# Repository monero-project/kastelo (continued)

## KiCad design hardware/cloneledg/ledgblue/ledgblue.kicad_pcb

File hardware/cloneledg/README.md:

# Hardware Cloneledg Design

One paragraph of descriptive text.

## Getting Started

Example text to help understand contents and subdirectories.

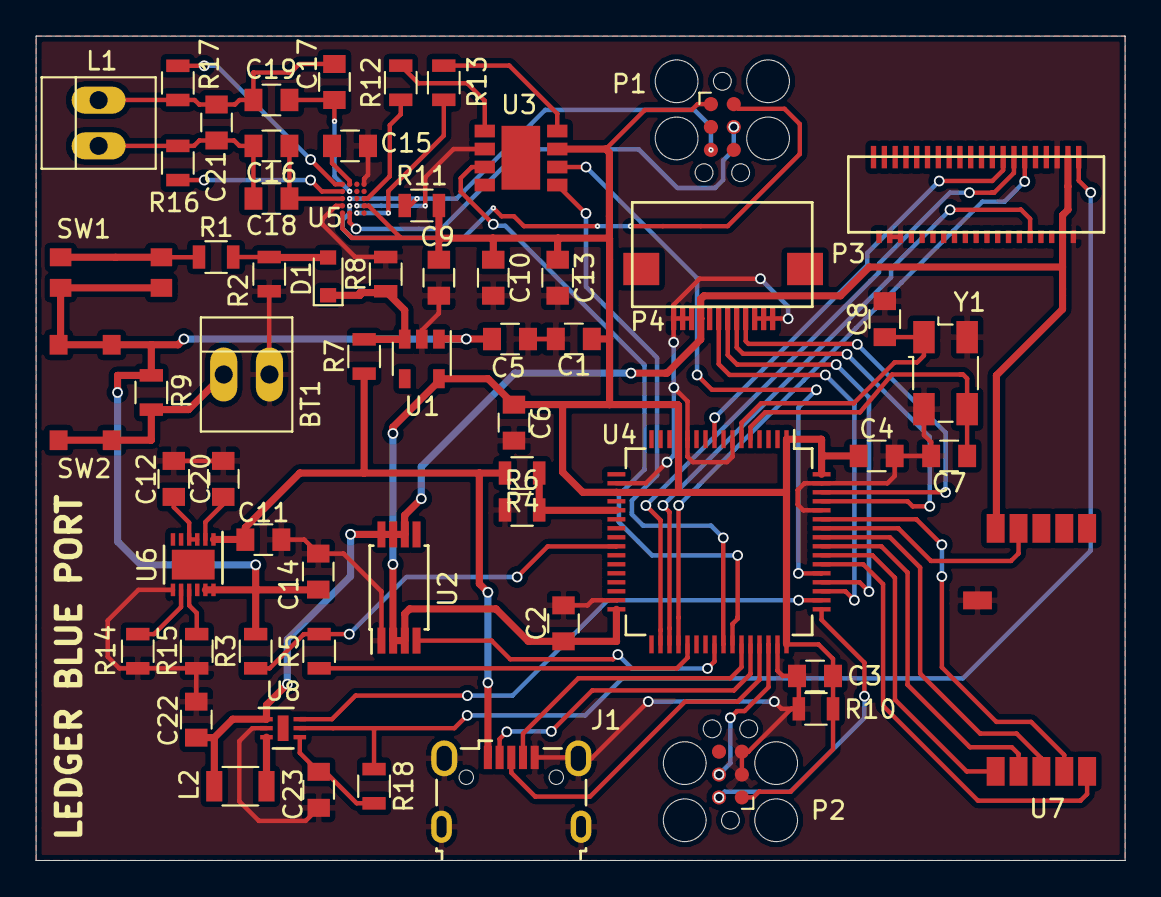
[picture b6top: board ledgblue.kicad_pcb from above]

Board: 2 copper layers, 60.5 x 45.8 mm, 61 parts (0 on the bottom side), 59 nets.

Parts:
BT1: Battery; PINHEAD1-2
C1, C2, C3, C4, C9, C13: 100nF; C_0805
C5, C6, C22, C23: 1uF; C_0805
C7, C8: 20pF; C_0805
C10, C14: 4.7uF; C_0805
C11, C12, C20: 2.2uF; C_0805
C15: 15nF; C_0805
C16, C17: 27pF; C_0805
C18, C19: 180pF; C_0805
C21: 39pF; C_0805
D1: D_Schottky; D_0805
J1: USB_OTG; USB_Micro-B_Wuerth-629105150521
L1: Antenna; PINHEAD1-2
L2: 10uH; L_1206
P1, P2: DEBUG; Tag-Connect_TC2030-IDC-FP
P3: YL035MY2; hiroseFH23-39S
P4: YL035MY2_TS_WURTH; wurth687-112-149-022
R1, R2, R14: 10k; R_0805
R3, R4, R5, R6: 1.2k; R_0805
R7: 680k; R_0805
R8: 1M; R_0805
R9, R12, R13, R16, R17: 0; R_0805
R10, R11: 100k; R_0805
R15: 1k; R_0805
R18: 10; R_0805
SW1: WURTH 436353045816; wurth436353045816
SW2: SW-PB; multicompMCFTE-3C-V
U1: LD39020_3.0V; SOT-23-5
U2: STMPS2151TTR; TSSOP-8_4.4x3mm_Pitch0.65mm
U3: ST31G480
U4: STM32L476RCT6; LQFP-64_10x10mm_Pitch0.5mm
U5: AMS_AS3921; amsAS3921
U6: STNS01PUR; DFN-12-1EP_3x3mm_Pitch0.45mm
U7: SPBTLE-RF; STSPBTLE-RF
U8: STLA02PUR; DFN-6-1EP_2x2mm_Pitch0.5mm
Y1: 8 MHz; Crystal_SMD_Abracon_ABM3B-4pin_5.0x3.2mm

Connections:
+BATT: C5.1, C14.2, R3.2, R9.1, SW1.1, SW2.1, U1.1, U6.11, U6.12
AUX_PWR: C22.2, L2.2, P3.3, P3.4, P4.9, U2.6, U2.7, U2.8, U7.5, U8.1
AUX_PWR_enable: U2.4, U4.40
BC_ADC_EN: R5.1, U4.37
BC_ADC_IN: R3.1, R5.2, U4.25
BLE_CS: U4.59, U7.10
BLE_IRQ: U4.58, U7.4
BLE_MISO: U4.56, U7.8
BLE_MOSI: U4.57, U7.9
BLE_RST: U4.54, U7.11
BLE_SCK: U4.55, U7.7
Backlight_PWM: U4.50, U8.6
ButtonIT: D1.2, R1.2, R2.1
DISP_SCL: P3.13, U4.34
Disp_CS: P3.10, U4.35
Disp_RESET: P3.15, U4.9
Disp_SDA: P3.11, U4.36
LED_A: P3.1, R18.1, U8.5
MAIN_POWER: C1.1, C2.1, C3.1, C4.1, C6.1, C9.1, C10.1, C13.1, P1.1, P2.1, R10.2, R11.2, U1.5, U2.2, U2.3, U3.7, U4.1, U4.13, U4.19, U4.32, U4.48, U4.64, U5.A4, U5.D5
NRST: BT1.2, C1.2, C2.2, C3.2, C4.2, C5.2, C6.2, C7.2, C8.2, C9.2, C10.2, C11.2, C12.2, C13.2, C14.1, C15.2, C20.1, C22.1, C23.2, J1.5, J1.6, P2.3, P2.5, P3.2, P3.5, P3.34, P3.36, P4.1, P4.2, P4.3, P4.10, P4.11, P4.12, R2.2, R6.1, R8.2, R10.1, R14.2, R15.2, U1.2, U2.1, U3.2, U4.7, U4.12, U4.18, U4.31, U4.47, U4.60, U4.63, U5.A1, U5.B1, U5.B4, U5.D4, U6.7, U7.6, U8.2, Y1.2, Y1.4
unnamed: BT1.1, R9.2, SW2.2
unnamed: C7.1, U4.5, Y1.3
unnamed: C8.1, U4.6, Y1.1
unnamed: C12.1, U6.2
unnamed: C15.1, U5.C1
unnamed: C16.1, C18.1, U5.D3
unnamed: C16.2, C18.2, C21.1, L1.1, R16.1
unnamed: C17.1, C19.1, U5.C2
unnamed: C17.2, C19.2, C21.2, L1.2, R17.1
unnamed: C20.2, U6.3, U6.4
unnamed: C23.1, R18.2, U8.4
unnamed: D1.1, R7.2, R8.1, U1.3
unnamed: L2.1, U8.3
unnamed: P1.2, U5.C4
unnamed: P1.4, U5.C5
unnamed: P1.5, R11.1, U5.C3
unnamed: R1.1, SW1.2
unnamed: R12.1, U5.A3
unnamed: R12.2, U3.1
unnamed: R13.1, U5.B5
unnamed: R13.2, U3.8
unnamed: R14.1, U6.8
unnamed: R15.1, U6.9
unnamed: R16.2, U5.D2
unnamed: R17.2, U5.D1
SE_CLK: U3.5, U4.41
SE_IO: U3.3, U4.42
SE_RST: U3.6, U4.53
SWCLK: P2.2, U4.49
SWIO: P2.4, U4.46
TS_CE: P4.7, U4.51
TS_IRQ: P4.6, U4.52
TS_SCL: P4.5, U4.61
TS_SDA: P4.4, U4.62
USBDM: J1.2, U4.44
USBDP: J1.3, U4.45
USBID: J1.4, U4.43
VBUS: C11.1, J1.1, R4.2, R7.1, U6.1
VBUS_PRE: R4.1, R6.2, U4.21

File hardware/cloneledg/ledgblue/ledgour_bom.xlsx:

| Ledgour BoM | Updated: 2018-01-07
 | Name | Package | Designation | Qty | Link | Alternative link
 | C1,C2,C3,C4,C9,C13 | C_0805 | 0.1uF | 6 | https://www.arrow.com/en/products/vj0805y104jxxcw1bc/vishay
 | C5,C6,C22,C23 | C_0805 | 1uF | 4 | https://www.arrow.com/en/products/vj0805y105jxqtw1bc/vishay
 | C7,C8 | C_0805 | 20pF | 2 | https://www.arrow.com/en/products/nmc0805npo200j50trpf/nic-c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
 | C10,C14 | C_0805 | 4.7uF | 2 | https://www.arrow.com/en/products/vj0805v475zxqtw1bc/vishay
 | C11,C12,C20 | C_0805 | 2.2uF | 3 | https://www.arrow.com/en/products/vj0805g225kxqtw1bc/vishay
 | C15 | C_0805 | 0.015uF | 1 | https://www.arrow.com/en/products/cl21b153kbannnc/samsung-el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
 | C16,C17 | C_0805 | 27pF | 2 | https://www.arrow.com/en/products/cl21c270jbannnc/samsung-el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
 | C18,C19 | C_0805 | 180pF | 2 | https://www.arrow.com/en/products/cl21c181jbannnd/samsung-el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
 | C21 | C_0805 | 39pF | 1 | https://www.arrow.com/en/products/cl21c390jbannnc/samsung-el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
 | R1,R2,R14 | R_0805 | 10k | 3 | https://www.arrow.com/en/products/crcw080510k0jnea/vishay
 | R3,R4,R5,R6 | R_0805 | 1.2k | 4 | https://www.arrow.com/en/products/crcw08051k20fkea/vishay
 | R7 | R_0805 | 680k | 1 | https://www.arrow.com/en/products/crcw0805680kfkea/vishay
 | R8 | R_0805 | 1M | 1 | https://www.arrow.com/en/products/crcw08051m00jneahp/vishay
 | R9,R12,R13,R16,R17 | R_0805 | 0 | 5 | https://www.arrow.com/en/products/rca08050000zsea/vishay
 | R10,R11 | R_0805 | 100k | 2 | https://www.arrow.com/en/products/crcw0805100kfkeb/vishay
 | R15 | R_0805 | 1k | 1 | https://www.arrow.com/en/products/crcw08051k00jnta/vishay
 | R18 | R_0805 | 10 | 1 | https://www.arrow.com/en/products/crcw080510r0jnea/vishay
 | BT1 | PINHEAD1-2 | Battery | 1 | https://www.arrow.com/en/products/0901200778/molex
 | L1 | PINHEAD1-2 | Antenna | 1 | https://www.arrow.com/en/products/0901200778/molex
 | L2 | L_1206 | 10uH | 1 | https://www.arrow.com/en/products/nlcv32t-100k-pfr/tdk
 | D1 | D_0805 | D_Schottky | 1 | https://www.arrow.com/en/products/sd0805s020s0r5/avx
 | SW1 | wurth436353045816 | WURTH 436353045816 | 1 | http://uk.farnell.com/wurth-elektronik/436353045816/switch-1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 | https://www.digikey.com/product-detail/en/wurth-electronics-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
 | SW2 | multicompMCFTE-3C-V | SW-PB | 1 | http://uk.farnell.com/multicomp/mcfte-3c-v/switch-micro-dete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
 | U1 | SOT-23-5 | LD39020 | 1 | https://www.arrow.com/en/products/ld39020adm30r/stmicroelectronics
 | U2 | TSSOP-8_4.4x3mm_Pitch0.65mm | STMPS2151TTR | 1 | https://www.arrow.com/en/products/stmps2151ttr/stmicroelectronics | https://www.mouser.de/ProductDetail/STMicroelectronics/STMPS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
 | U3 | WLCSP | ST31G480 | 1 | N/A to due NDA
 | U4 | LQFP-64_10x10mm_Pitch0.5mm | STM32L476RCT6 | 1 | https://www.arrow.com/en/products/stm32l476rct6/stmicroelectronics
 | U5 | amsAS3921 | AMS_AS3921 | 1 | https://www.arrow.com/en/products/as3921-bwlt/ams-ag | https://www.mouser.de/ProductDetail/ams/AS3921-BWLM/?qs=16w8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
 | U6 | DFN-12-1EP_3x3mm_Pitch0.45mm | STNS01PUR | 1 | https://www.arrow.com/en/products/stns01pur/stmicroelectronics
 | U7 | STSPBTLE-RF | SPBTLE-RF | 1 | https://www.arrow.com/en/products/spbtle-rf/stmicroelectronics | https://www.mouser.de/ProductDetail/STMicroelectronics/SPBTL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
 | U8 | DFN-6-1EP_2x2mm_Pitch0.5mm | STLA02PUR | 1 | https://www.arrow.com/en/products/stla02pur/stmicroelectronics | https://www.mouser.de/ProductDetail/STMicroelectronics/STLA0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
 | Y1 | 4pin_5.0x3.2mm | Abracon_ABM3B_8MHz | 1 | https://www.arrow.com/en/products/abm3b-8.000mhz-b2-t/abracon
 | P1,P2 | Tag Connect TC2030-IDC | Tag Connect TC2030-IDC | 2 | http://www.tag-connect.com/TC2030-IDC
 | P3 | hiroseFH23-39S | YL035MY2 | 1 | https://www.mouser.de/ProductDetail/?qs=0N%252bVULUZFj%2fgb7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
 | P4 | wurth687-112-149-022 | YL035MY2_TS_WURTH | 1 | https://www.mouser.de/ProductDetail/Wurth-Electronics/687112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
 | J1 | USB_Micro-B | Wuerth-629105150521 | 1 | https://www.mouser.de/productdetail/wurth-electronics/629105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

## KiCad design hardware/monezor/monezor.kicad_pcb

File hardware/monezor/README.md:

## Monezor Design Status

This was the monezor hw wallet PCB revision control.

New development of STM32 based designs throughout the project stopped after the Julian Candy released hardware revision 0.2.0.

## Exit Reasoning

STM32 integration stopped as the architecture (at least M3 based MCUs) failed to meet expectations, as well as better architectures with immutable boot and hardware cryptography appeared.

## Maintenance Plan

STM32 design is maintained in the (developer edition) Breakneck codebase, for those who prefer the architecture opposed to the advanced and improved one found in the tip master of revision control.

To find the STM32 based Breakneck codebase, switch to the _revstm_ branch:

```
$ git checkout revstm
$ cd hardware/breakneck
```

## Development Plan

New features are found in the Breakneck master codebase which migrates logic to a new consumer edition codebase as UX and functional testing mandates.

To find the current Breakneck codebase, switch to the _master_ branch:

```
$ git checkout master
$ cd hardware/breakneck
```

## New Architecture

Although nRF52840 is a candidate, the replacement for STM32 parts in new designs is CEC1702.

## Preservation Plan

The STM32 based Monezor codebase is preserved in the _revstm_ branch.

## Glossary

- **Consumer edition:** One of two Monero dedicated hardware wallet editions, integrating a well tested subset of features from the developer edition.
- **Developer edition:** One of two Monero dedicated hardware wallet editions, including all features. For example, the developer edition may contain experimental intrusion detection while the consumer edition may not (unless the features are proven stable and useful.)
- **Monezor:** The model name associated with the consumer edition.
- **Breakneck:** The model name associated with the developer edition.
- **Julian Candy:** A code name corresponding with a range of hardware revisions including 0.2.0.
- **Extra Tabulo:** A code name corresponding with a range of hardware revisions including 0.9.0.

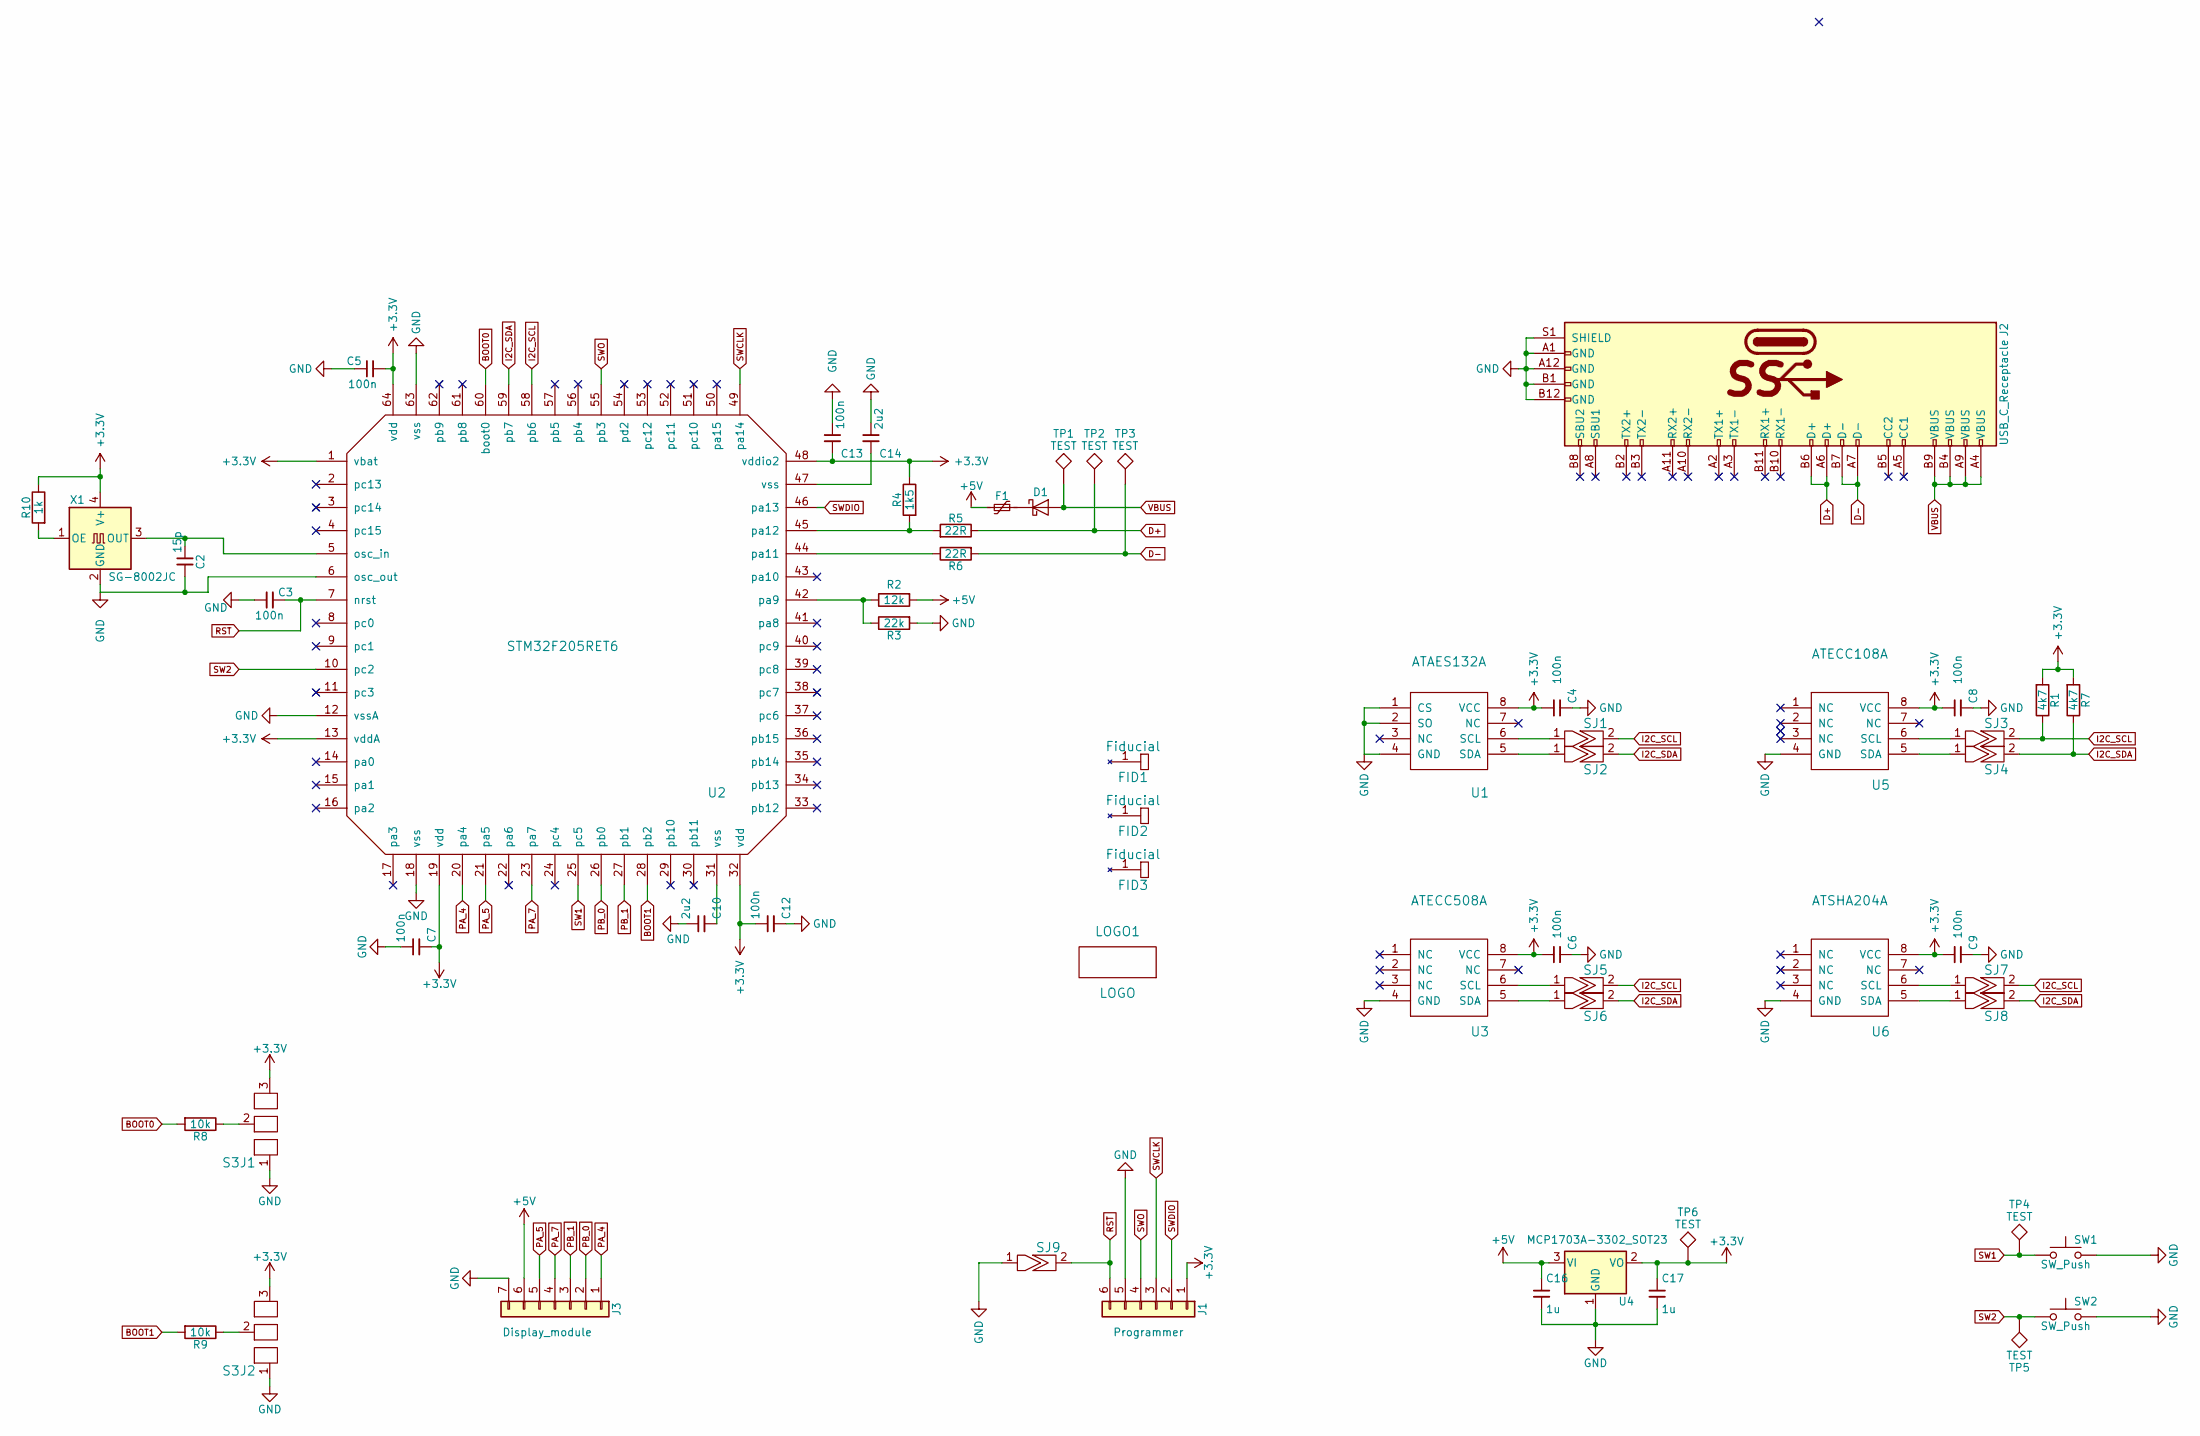
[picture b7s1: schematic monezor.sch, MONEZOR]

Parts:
C2: 15p; SMD_0805
C3, C5, C7, C12, C13: 100n; SMD_0805
C4, C6, C8, C9: 100n; SMD_0805_bottom
C10, C14: 2u2; SMD_0805
C16, C17: 1u; SMD_0805
D1: D_Schottky; D_SOD-523
F1: Polyfuse_Small; SMD_0805
FID1, FID2, FID3: Fiducial; Fiducial_Modern_SilkscreenTop
J1: Programmer; Pin_Header_Straight_1x06_Pitch2.54mm
J2: USB_C_Receptacle; USB_C_Receptacle_Amphenol_12401548E4-2A
J3: Display_module; Pin_Header_Straight_1x07_Pitch2.54mm
LOGO1: LOGO; xmr_logo
R1, R7: 4k7; SMD_0805
R2: 12k; SMD_0805
R3: 22k; SMD_0805
R4: 1k5; SMD_0805
R5, R6: 22R; SMD_0805
R8, R9: 10k; SMD_0805
R10: 1k; SMD_0805
S3J1, S3J2: solder_jumper_3pin; solder_jumper_3pin_tht_2.54
SJ1, SJ2, SJ3, SJ4, SJ5, SJ6, SJ7, SJ8: solder_jumper; solderjumper_bottom
SJ9: solder_jumper
SW1, SW2: SW_Push; BUTTON_SWITCH_SW_SPST_EVPBF
TP1, TP2, TP3, TP4, TP5, TP6: TEST; Test_Point_THT
U1: ATAES132A; SO-8_3.9x4.9mm_Pitch1.27mm_bottom
U2: STM32F205RET6; TQFP-64_10x10mm_Pitch0.5mm
U3: ATECC508A; SO-8_3.9x4.9mm_Pitch1.27mm_bottom
U4: MCP1703A-3302_SOT23; SOT-23
U5: ATECC108A; SO-8_3.9x4.9mm_Pitch1.27mm_bottom
U6: ATSHA204A; SO-8_3.9x4.9mm_Pitch1.27mm_bottom
X1: SG-8002JC; Oscillator_SMD_IQD_IQXO70-4pin_7.5x5.0mm

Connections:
+3V3: C4.2, C5.2, C6.2, C7.1, C8.2, C9.2, C12.2, C13.1, C17.1, J1.1, R1.2, R4.1, R7.2, R10.1, S3J1.3, S3J2.3, TP6.1, U1.8 (VCC), U2.1 (vbat), U2.13 (vddA), U2.19 (vdd), U2.32 (vdd), U2.48 (vddio2), U2.64 (vdd), U3.8 (VCC), U4.2 (VO), U5.8 (VCC), U6.8 (VCC), X1.4 (V+)
+5V: C16.1, F1.2, J3.6, R2.2, U4.3 (VI)
BOOT0: R8.2, U2.60 (boot0)
BOOT1: R9.2, U2.28 (pb2)
D+: J2.A6 (D+), J2.B6 (D+), R5.1, TP2.1
D-: J2.A7 (D-), J2.B7 (D-), R6.2, TP3.1
GND: C2.1, C3.2, C4.1, C5.1, C6.1, C7.2, C8.1, C9.1, C10.2, C12.1, C13.2, C14.2, C16.2, C17.2, J1.5, J2.A1 (GND), J2.A12 (GND), J2.B1 (GND), J2.B12 (GND), J2.S1 (SHIELD), J3.7, R3.2, S3J1.1, S3J2.1, SJ9.1, SW1.2, SW2.2, U1.1 (CS), U1.2 (SO), U1.4 (GND), U2.6 (osc_out), U2.12 (vssA), U2.18 (vss), U2.63 (vss), U3.4 (GND), U4.1 (GND), U5.4 (GND), U6.4 (GND), X1.2 (GND)
I2C_SCL: R1.1, SJ1.2, SJ3.2, SJ5.2, SJ7.2, U2.58 (pb6)
I2C_SDA: R7.1, SJ2.2, SJ4.2, SJ6.2, SJ8.2, U2.59 (pb7)
unnamed: C2.2, U2.5 (osc_in), X1.3 (OUT)
unnamed: C10.1, U2.31 (vss)
unnamed: C14.1, U2.47 (vss)
unnamed: D1.1 (K), F1.1
unnamed: R2.1, R3.1, U2.42 (pa9)
unnamed: R4.2, R5.2, U2.45 (pa12)
unnamed: R6.1, U2.44 (pa11)
unnamed: R8.1, S3J1.2
unnamed: R9.1, S3J2.2
unnamed: R10.2, X1.1 (OE)
unnamed: SJ1.1, U1.6 (SCL)
unnamed: SJ2.1, U1.5 (SDA)
unnamed: SJ3.1, U5.6 (SCL)
unnamed: SJ4.1, U5.5 (SDA)
unnamed: SJ5.1, U3.6 (SCL)
unnamed: SJ6.1, U3.5 (SDA)
unnamed: SJ7.1, U6.6 (SCL)
unnamed: SJ8.1, U6.5 (SDA)
PA_4: J3.1, U2.20 (pa4)
PA_5: J3.5, U2.21 (pa5)
PA_7: J3.4, U2.23 (pa7)
PB_0: J3.2, U2.26 (pb0)
PB_1: J3.3, U2.27 (pb1)
RST: C3.1, J1.6, SJ9.2, U2.7 (nrst)
SW1: SW1.1, TP4.1, U2.25 (pc5)
SW2: SW2.1, TP5.1, U2.10 (pc2)
SWCLK: J1.3, U2.49 (pa14)
SWDIO: J1.2, U2.46 (pa13)
SWO: J1.4, U2.55 (pb3)
VBUS: D1.2 (A), J2.A4 (VBUS), J2.A9 (VBUS), J2.B4 (VBUS), J2.B9 (VBUS), TP1.1

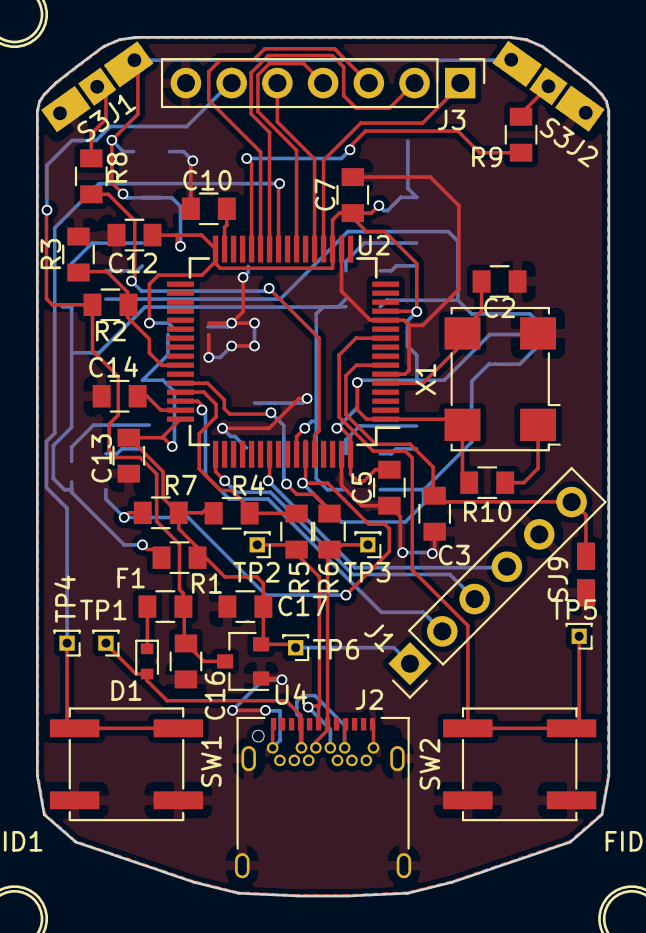
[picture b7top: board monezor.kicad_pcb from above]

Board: 2 copper layers, 31.8 x 47.7 mm, 59 parts (0 on the bottom side), 39 nets.

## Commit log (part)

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2017-10-18 Improved (enough?) location name for MCUDev derived design.
2017-10-18 Created contributing guidance document.
2017-11-10 Included location for FPGA design support and custom logic.
2017-11-11 Directed to track files in both classic and modelt versions.
2017-11-12 Hopefully practice pull request and merge workflow in team.
2017-11-12 Build in documentation of hard to remember pull request merge procedure.
2017-11-13 Correct flawed URL to avoid a HTTP 404.
2017-11-14 Added overlooked command to remove a dangling pull request branch.
2017-11-14 Created rudimentary graphics for use in print and online promotion.
2017-11-15 Created location for forthcoming antenna design in case of RF development.
2017-11-16 schematics added
2017-11-17 Created a Julian Candy manufacturing panel for single board design.
2017-11-18 Corrected minor grammar use of subject verb 'Users acknowledge.'
2017-11-19 [Task-119] Demisreablise our repository, created boilerplate (sub)titles.
2017-11-19 Edited a bit to remove accidental Kovri project residue and some 404 links.
2017-11-20 Flexible bluetooth antenna
    Flextenna BT (flexible bluetooth antenna) based on Kapton substrate, optimized for a center frequency of 2.45 GHz.
2017-11-20 Added vector exported graphics for mechanical engineering fabrication.
2017-11-20 Added installation instructions
2017-12-05 Cleaning up of file names
    Cleaned up the readme.md and filenames a bit.
2017-12-07 Cleaned up sources a bit, removing backup files and sanitised user accounts.
2017-12-09 Layout has been compacted
    The layout has been shrunk a bit. A pin header is used as placeholder for the antenna. NFC chip still not connected.
2017-12-19 Decrudified by making path names consistent and removing untracked backups.
2017-12-23 [Issue 61: Updated logo]
    A logo design suggestion for the hardware wallet project.
2017-12-31 initial blank fw
2017-12-31 submodules tweaking
2017-12-31 Corrected submodules configuration after changing subdirectory structures.
2018-01-04 Documented USB identification information pending upstream vendors.
2018-01-05 cleared warnings
2018-01-07 Reflect new USB identifiers in code pending upstream authority approval.
2018-01-07 Removed old files, after completed versions appeared named 'ledgour_bom'.
2018-01-07 usb first hello world attempts
2018-02-08 Modified to additionally avoid tracking of files in subdirectories.
2018-02-08 Corrected name of repository to recently chosen new name.
2018-02-08 Improved readme information by correcting graphic link and enlarging photos.
2018-02-10 Included display connector and Monero logo footprints in local database.
2018-02-10 Drew edge cuts, display concept, boilerplate, and dimensions.
2018-02-10 Implicitly associated default footprint for Monero logo library symbol.
2018-02-15 Corrected flawed OLED_D(0|1) anchor labels to logical display connections.
2018-02-17 Replaced a DNP zero ohm resistor with a more appropriate solder jumper.
2018-02-24 OLED: define SPISend
    - adds definition for SPISend
2018-02-26 Reluctantly added raster graphic sources for silkscreen solder mask legends.
2018-02-28 Added local copies of 3D shapes, made footprint location consistent to native KiCad, and changed holes.
2018-03-03 Corrected scaling and rotation of shapes, and connected ground paths.
2018-03-04 Moved C3 from under SW1, removed redundant SW traces, and aligned vias.
2018-03-04 Resolved unconnected bootloader and reset pins, and improved 3V3 and GND.
2018-03-05 Added pdf schematics of current design
2018-03-07 Reduced no connects further, implementing connections to +3V3 leads.
2018-03-07 Eliminated all ground lead no connect errors from the design rule check.
2018-03-08 Corrected SOT-23 3D shape absolute path, removing step and adding wings.
2018-03-08 Regenerated PDF copy of vector schematic master file.
2018-03-10 Corrected nonportable library, module, and model descriptors.
2018-03-11 Improved reset circuit by replacing with low profile angled hardware.
2018-03-15 Add disclaimer for testnet funds
2018-03-17 Added supporting structures (library, footprint, and doc) for light sensor.
2018-03-18 Integrated missing battery clip and provisional tap detector circuit.
2018-03-18 Added supporting structures (library, footprint, and model) for touch sensor.
2018-03-19 Worked around hard copy transparent background worksheet defects.
2018-03-20 Replaced hand solder DS1 with FPC connector, supporting archives only.
2018-03-25 Corrected contact numbering according to ER-OLED013A1-1W datasheet.
2018-03-27 Completed and corrected models, removed easteregg, and included datasheets.
    A number of funky hacks allow for 3D model rendering to look good, by
    specifying similar shaped packages for lacking models such as LGA-2mm
    and 6-pin LED chips. I hacked the rendering even more to represent a
    battery clip that's not the one in use at all, which could be misleading.
2018-04-01 Included recent enclosure concept sketch for Monezor consumer edition.
2018-07-15 Completed integrating and formatting ajs new text for 4-up printing.
2018-07-29 Included attribution question and answer to FAQ and bumped version.
2018-09-11 Initialised and completed first prototype design of a USB-C tester.
2018-10-09 Do a live on site conference badge super commital #HCPP18, integrating hardware design sources for the conference badge.
2018-10-25 Included prime platine changes and bump version for imminent tagging.
2018-10-25 Dumped CEC mix remastering of post STM (MCU) maintenance branching.
2018-10-26 Removed unused voltage regulator with plans to leverage CP2102N LDO.
2018-10-26 Annotated missing fiducial symbol fields in number ordered fashion.
2018-10-26 Added for USB logic a ESD protection part and supporting circuits.
2018-10-26 According to some sources, a undocumented feature is test point on NC 10.
2018-10-27 Annotated with temporary markings for PnP rails and speculative VDD.
2018-10-28 Prepared for integration of SPI quad flash storage EEPROM.
2018-10-28 Prepared for VBAT backed up state by adding CR1220 support structures.
2018-10-28 Included Dediprog (or Aardvark) compatible host adapter SPI connector.
2018-10-29 Corrected mistaken duplicate crystal resonator input entries.
2018-10-30 Documented dimensions of a typical 500 mAh 3V7 LiPo battery.
2018-10-30 Improved display connection and orientation while freeing ADC port.
2018-10-30 Removed unused (after last crystal commit) symbols and footprints.
2018-10-30 Implemented tactile switch and preliminary detector switch circuits.
2018-11-03 Implemented security enhancement as per in 4,2 ECC508 Interface Pins, specified in document CEC1702 ROM Description Addendum, Table 4-2 CEC1702 ECC508 Interface Pins.
2018-11-03 Completed CW victim south connections according to CW308_UFO_Target.
2018-11-04 Removed unused 0.7mm display pads and prepared for 24-pin additions.
2018-11-06 Annotated recently added test points pending renewed ERC testing.
2018-11-06 Added missing WFBGA footprint and shape models for CEC1702 layout.
2018-11-07 Corrected a last time towards staging display connectors before moving.
2018-11-08 Corrected missing, flawed, and other footprint package changes.
2018-11-08 Renumbered annotations to clean netlist pending start of layout.
2018-11-09 Corrected flawed symbol named with slash characters to remove them.
2018-11-09 Updated according to schematic footprint changes and added descriptions.
2018-11-10 Changed JTAG footprint, improved SAO legend, and corrected models.
2018-11-10 Made a controlled dump of recent layout changes pending arrangement.
2018-11-12 Modified trace widths and vias for consistency with design rules.
2018-11-17 Completed breakout (only betweeen edge connectors) of JTAG circuits.
2018-12-04 Regenerated netlist to accommodate recent schematic additions.
2018-12-05 Created a six up Stencil8 compliant panel using mousebite tabs.
2018-12-08 Completed conversion of manufacturing positions to special requirement.
2018-12-10 Added early state of information relating to host software plans.
2018-12-17 Integrated hex nut mounts, board guides, and adjusted length.
2018-12-24 Added enclosure top to complement bottom shell open arrangement.
2018-12-29 Released a prototype grade 35C3 badge design live on site.
2018-12-31 Documented unconnected parts to reduce unintentional short circuits.
2018-12-31 Flushed current changes to accommodate results of recent assembly tests; Introduced plastics engineering resources, made fiducial marks SMT for placing, merged SMT attribute to panel design according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
2018-12-31 Cherrypick merged 97c0734: Corrected broken link to raster circuit...
2019-01-01 Completed preparation of solderjumper integration for USBC debugging.
2019-01-03 Manually processed and recommitted placement position files.
2019-01-03 Updated page document reflecting recent graphic rendering additions.
2019-01-07 Optimised colour palette and storage using an animation filter.
2019-01-07 Increased clearanance, added license text, and made improvements.
2019-01-07 Included explicit attribution to contributors, long overdue sorry.
2019-01-07 Upgraded symbol based formats and constructs to conform with Kicad 5.0.
2019-01-07 Merged first part of bf3d6d9, debug reduction of USBC unused pins.
2019-01-07 Corrected rendered model paths and improved boot circuit silkscreen.
2019-01-07 Removed outdated prices, added potting compound, and conformal coating.
2019-01-07 Added missing minimised USB symbol structures to correct schematic.
2019-01-08 Reworked input pullups, USB-C connector, and corrected display model.
2019-01-08 Corrected solderjumpers by removing unnecessary paste layers.
2019-01-08 Added manufacturer part numbers and Octopart identifiers as needed.
2019-01-13 Merged from branch 'revstm' selective commit dc71e6a.
2019-01-13 Merged db2f2b8 from 'master' slide switch (hack) and circuitry.
2019-01-14 Corrected last remaining bottom fiducials to top and removed footprint.
2019-01-14 Included git filter configuration to control irrelevant state change.
2019-01-14 Merged 8cd1b5c from 'master' to try to control irrelevant state change.
2019-01-14 Improved file tracking ignore configuration to complete closed packages.
2019-01-17 Corrected incompatible SE (608A) timing in ROM assistance.
    This follows advice taken from Microchip case 00347747, warning against
    replacing the CEC1702 ROM addendum specification of ATECC508A with the
    more capable ATECC608A SE.
2019-01-18 Corrected only slightly flawed part make and model.
2019-01-18 Recorrected CC line pulldowns to comply with AN4775.
2019-01-18 Improve reminder message for tamper pin detector switch.
2019-01-22 Adjusted again to accommodate detector height after testing.
2019-01-23 Rerouted improved power circuit of UART bridge.
2019-02-12 Added corner pad brims to mitigate hot plate curling.
2019-02-16 Improved wording of recent STM32 integration SWD remark.
2019-03-06 Documented suspected USB controlling problem regarding HSE and LSE.
2019-03-07 Replaced SW1 to PC3(TQFP64/11) to move away from existing crystals.
2019-03-09 Added second display connector for 24-pin variants.
    This change integrates reference designs intended for 30-pin connectors
    as found in download/interfacing/ER-OLED0.96_Series_Interfacing.pdf
2019-03-28 Integrated a MCP73831 controlled lithium ion battery charger circuit.
2019-04-15 Improved annotation of untested BOOT1 pulldown circuit.
2019-04-26 Added new devkit design decoration with a lift tab adjustment?
2019-06-21 Initialised a standard PlatformIO project to host firmware sources.
2019-11-30 Dump version generated project changes pending project migration.
2019-12-02 Combined top and bottom layers for positioning import and documented.
2019-12-05 Added a second 0,2mm layer to text areas to reinforce clarity.
2019-12-12 Removed dark coloured text backing and added a layer to text outlines.
2019-12-14 Corrected resin symbol surface replaced at top of floor thickness.
2019-12-14 Added missing layout symbols for complete automated placement.
2019-12-20 Reduced height from 16mm to 15mm and corrected flawed constraints.
2019-12-21 Corrected flawed calculation of hexnut diameter to use the spreadsheet.
2020-01-02 Renamed to consistently avoid whitespace in filenames and corrected typo.
2020-01-05 Modified text to better state chapter and rules, improving english.
2020-01-21 Corrected wall thickness of upper connector pocket for FDM process.
